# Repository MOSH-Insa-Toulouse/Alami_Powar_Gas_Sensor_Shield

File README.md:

**MOSH - Smart Devices – Arduino Gas Sensor Shield**

This project was completed as part of the &quot;Smart Devices&quot; Course of the Mastère spécialisé Innovative and secure IoT systems at INSA Toulouse.

**By :** _Amine Alami And Rameshwari Powar_

**Project Description**

- The aim of the project is to design an Arduino shield that incorporates a nanoparticle gas sensor and a RN2483 LoRa Module, which allows data from the gas sensor to be transmitted to a LoRa Gateway, through which it can be uploaded to the Cloud or a local network.
- The Arduino Gas Sensor Shield was designed using KiCad, a printed circuit board (PCB) design software package.
- The Shield can be used with Arduino UNO or other similar microcontroller kits, such as the Genuino 101.
- The Shield has a socket through which a RN2483-based LoRa Module could be plugged.

**CONTENT:**

**Design Files**

1. Schematic Diagram
2. PCB Footprint Layout
3. PCB 3D Layout

**Design Files**

1. **Schematic Diagram**

- Design Procedure

- We created a symbol for Operational Amplifier (LTC1050) and the RN2483 LoRa Module (RN2483\_Breakout) using KiCAD&#39;s symbol editor. We then assigned the footprint for the OpAmp and assigned an 8-pin socket as the footprint of the RN2483 LoRa Module.

- We drew the circuit diagram for the OpAmp Signal conditioning circuit (for impedance matching). The gas sensor was modelled as a resistor (RSensor1) in the circuit diagram. The footprint of the gas sensor was assigned to the TO-5-4 package (which is a casing in which the nanoparticle gas sensor will be put).

- The I/O of the Arduino Shield sockets were connected to the RN2483 LoRa Module and to the output of the impedance matching circuit.

- Schematic components

- The input resistor R1 - protects amplifier from electrostatic discharges.
- The capacitor C1 and the resistor R2 - filter the current noise.
- The capacitor C3 - filters the noise from the voltage input 5V.
- The resistor R4 – resistance at output of the amplifier.
- The resistor R5 and the capacitor C4 is a low-pass filter at the output of the assembly.
- The Rsensor1 - represents the gas sensor

1. **PCB Footprint Layout**

- Design Procedure

- Created a netlist from the schematic.
- Then we imported the components from the created netlist.
- We set design rules and set the track width of 0.8 mm and 1 mm for voltages
- We added a Ground Plane on the back
- Finally routed each components by wires

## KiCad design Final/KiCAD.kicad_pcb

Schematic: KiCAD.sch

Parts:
C1, C2, C3: 100n; C_Rect_L4.6mm_W2.0mm_P2.50mm_MKS02_FKP02
C4: 1u; C_Rect_L4.6mm_W2.0mm_P2.50mm_MKS02_FKP02
P1: Power; Socket_Strip_Arduino_1x08
P2: Analog; Socket_Strip_Arduino_1x06
P3: Digital; Socket_Strip_Arduino_1x10
P4: Digital; Socket_Strip_Arduino_1x08
P5, P6, P7, P8: CONN_01X01; Arduino_1pin
R1, R3: 100k; R_Axial_DIN0204_L3.6mm_D1.6mm_P1.90mm_Vertical
R5: 10k; R_Axial_DIN0204_L3.6mm_D1.6mm_P1.90mm_Vertical
R6: 1k; R_Axial_DIN0204_L3.6mm_D1.6mm_P1.90mm_Vertical
RN2483: LoRa Module; PinSocket_1x08_P2.54mm_Vertical
RSensor1: 10k; TO-5-4
Rcal1, Rcal2: R; R_Axial_DIN0204_L3.6mm_D1.6mm_P1.90mm_Vertical
U1: LTC1050; DIP-8_W7.62mm_LongPads

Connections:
+3V3: P1.4, RN2483.6 (3V3), RSensor1.1
+5V: C3.1, P1.5, U1.7 (V+)
/2: P4.6
/3(**): P4.5
/4: P4.4
/5(**): P4.3
/6(**): P4.2
/7: P4.1
/8: P3.10
/9(**): P3.9
/10(**/SS): P3.8
/11(**/MOSI): P3.7
/12(MISO): P3.6
/13(SCK): P3.5
/A1: P2.2
/A2: P2.3
/A3: P2.4
/A4(SDA): P3.2
/A5(SCL): P3.1
/AREF: P3.3
/IOREF: P1.2
/Reset: P1.3
/Vin: P1.8
A0: C2.1, P2.1, R6.1
GND: C1.2, C2.2, C3.2, P1.6, P1.7, P3.4, R1.2, RN2483.8 (GND), Rcal2.2, U1.4 (V-)
unnamed: C1.1, R1.1, R5.2, U1.3 (+IN)
unnamed: C4.1, R3.1, R6.2, U1.6 (Out)
unnamed: C4.2, R3.2, Rcal1.1, U1.2 (-IN)
unnamed: R5.1, RSensor1.2
unnamed: Rcal1.2, Rcal2.1
RX: P4.8, RN2483.2 (RX)
TX: P4.7, RN2483.1 (TX)

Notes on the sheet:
Holes

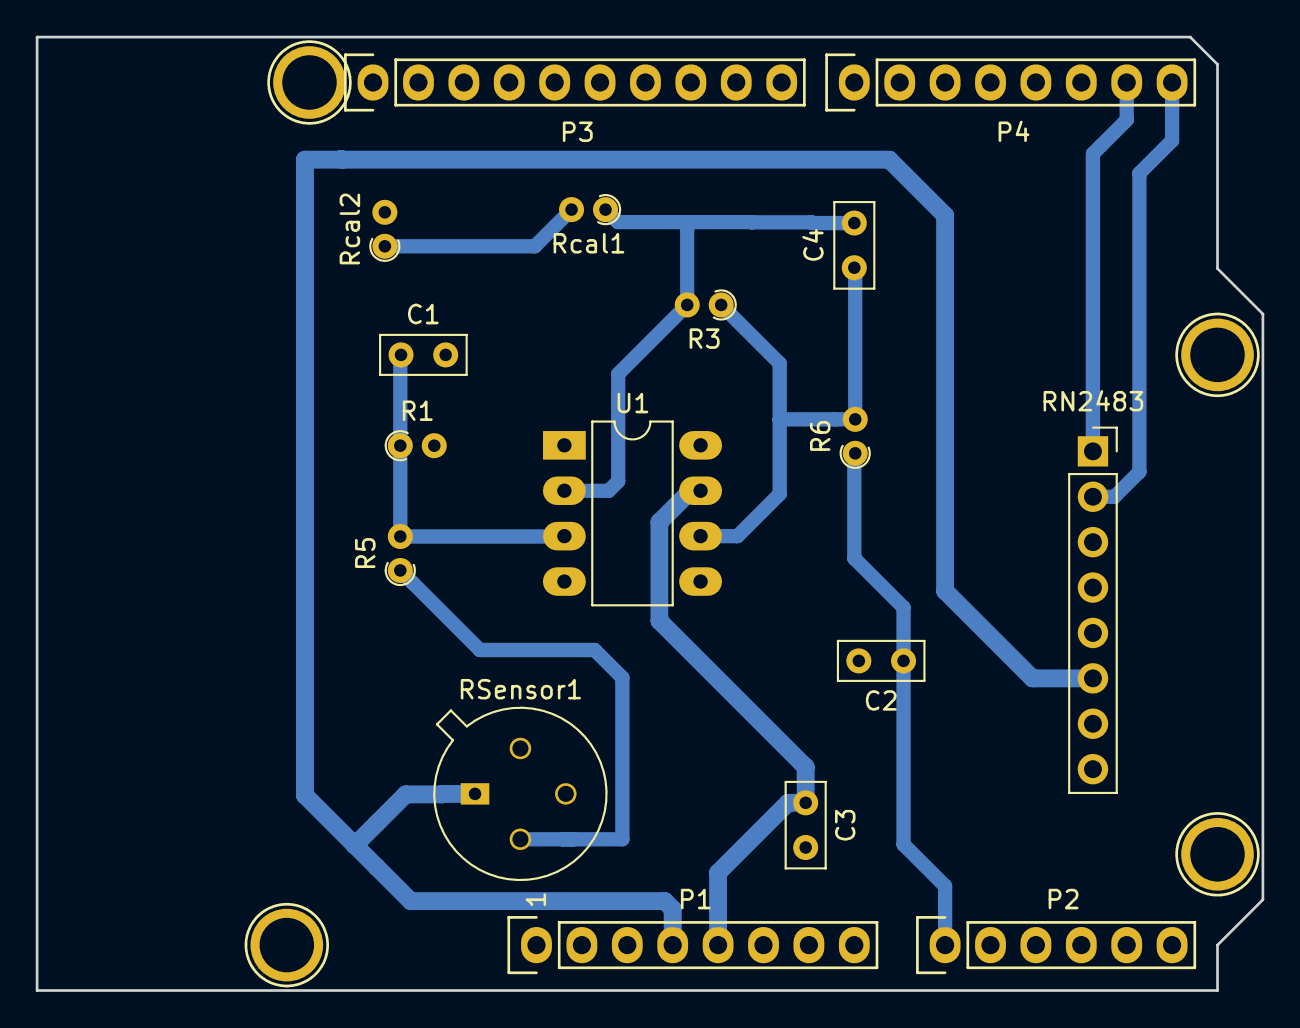
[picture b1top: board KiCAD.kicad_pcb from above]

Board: 2 copper layers, 68.6 x 53.3 mm, 21 parts (0 on the bottom side), 11 nets.
